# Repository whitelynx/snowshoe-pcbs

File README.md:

Snowshoe PCBs
=============

Snowshoe Single Keyswitch Hotswap Boards

Some very simple PCBs to make it easier to work with Kailh MX or Choc hotswap sockets.

---

I've used Kailh MX hotswap sockets in my keyboard designs for a while; I really value the flexibility of being able to
swap out my switches. However, since my keyboard designs are not flat, I can't just use a standard full-size PCB for my
keyboard. This allows me to have individual PCBs for each switch for better support, and makes it easier to solder to
them instead of having to solder leads to the hotswap sockets directly.

This was directly inspired by my work on [the Dactyl Lynx keyboard][], and the latest version of that keyboard uses
these boards. (37 per side)

This project is released under the terms of the [CERN Open Hardware Licence Version 2 - Weakly Reciprocal][]; see
`LICENSE` for the full text of the license.

[the Dactyl Lynx keyboard]: https://hackaday.io/project/176016-dactyl-lynx
[CERN Open Hardware Licence Version 2 - Weakly Reciprocal]: https://spdx.org/licenses/CERN-OHL-W-2.0.html

---

Resources
---------

This KiCad project uses the following resources:

Parts:
- [keyswitches.pretty](https://github.com/daprice/keyswitches.pretty)

Graphics:
- [Open Source Hardware Logo by Macklin Chaffee](https://oshwa.org/resources/open-source-hardware-logo/)

3D Models:
- [Kailh Hot swap socket by Baco](https://grabcad.com/library/kailh-hot-swap-socket-1)
- [Kailh 1350 socket by Dennis Lee](https://grabcad.com/library/kailh-1350-socket-2)

---

History
-------

This project was originally created in Flux.ai, but has now been ported to KiCad. You can find the original Flux.ai
projects here:

- [Snowshoe MX (old)](https://www.flux.ai/whitelynx/mx-single-keyswitch-hot-swap-board)
- [Snowshoe MX panel (old)](https://www.flux.ai/whitelynx/mx-single-keyswitch-hot-swap-board-panel)
- [Snowshoe Choc (old)](https://www.flux.ai/whitelynx/choc-single-keyswitch-hot-swap-board)
- [Snowshoe Choc panel (old)](https://www.flux.ai/whitelynx/choc-single-keyswitch-hot-swap-board-panel)

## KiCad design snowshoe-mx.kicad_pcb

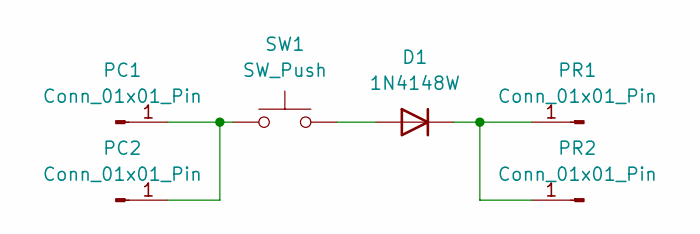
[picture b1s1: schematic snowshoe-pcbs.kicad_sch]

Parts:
D1: 1N4148W; D_SOD-123
PC1, PC2: Conn_01x01_Pin; Pin_D0.7mm_L6.5mm_W1.8mm_FlatFork
PR1, PR2: Conn_01x01_Pin; Pin_D0.7mm_L6.5mm_W1.8mm_FlatFork
SW1: SW_Push; Kailh_socket_MX

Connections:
unnamed: D1.2 (A), SW1.2
unnamed: D1.1 (K), PR1.1, PR2.1
unnamed: PC1.1, PC2.1, SW1.1

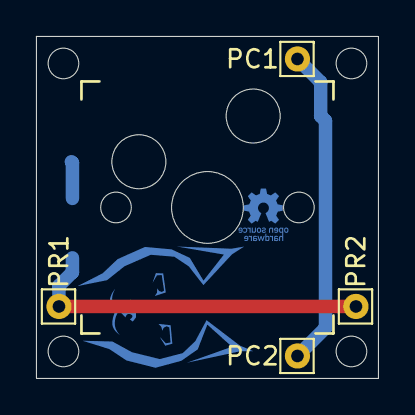
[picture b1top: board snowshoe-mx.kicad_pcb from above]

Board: 2 copper layers, 19.0 x 19.0 mm, 6 parts (1 on the bottom side), 3 nets.

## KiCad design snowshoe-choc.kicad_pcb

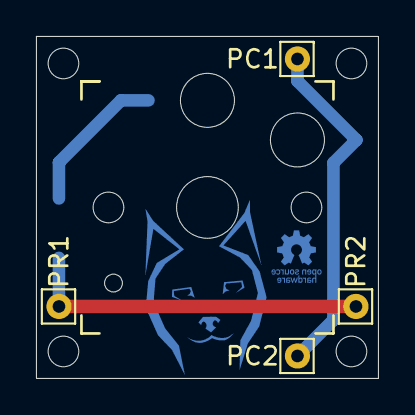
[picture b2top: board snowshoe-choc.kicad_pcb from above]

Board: 2 copper layers, 19.0 x 19.0 mm, 6 parts (1 on the bottom side), 3 nets.

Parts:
D1: 1N4148W; D_SOD-123
PC1, PC2: Conn_01x01_Pin; Pin_D0.7mm_L6.5mm_W1.8mm_FlatFork
PR1, PR2: Conn_01x01_Pin; Pin_D0.7mm_L6.5mm_W1.8mm_FlatFork
SW1: SW_Push; Kailh_socket_PG1350

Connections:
unnamed: D1.2 (A), SW1.1
unnamed: D1.1 (K), PR1.1, PR2.1
unnamed: PC1.1, PC2.1, SW1.2

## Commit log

2025-06-04 Initial port to KiCad
2025-06-04 Corrected image URLs

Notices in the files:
snowshoe-choc.kicad_pcb:
License: CERN-OHL-W-2.0
